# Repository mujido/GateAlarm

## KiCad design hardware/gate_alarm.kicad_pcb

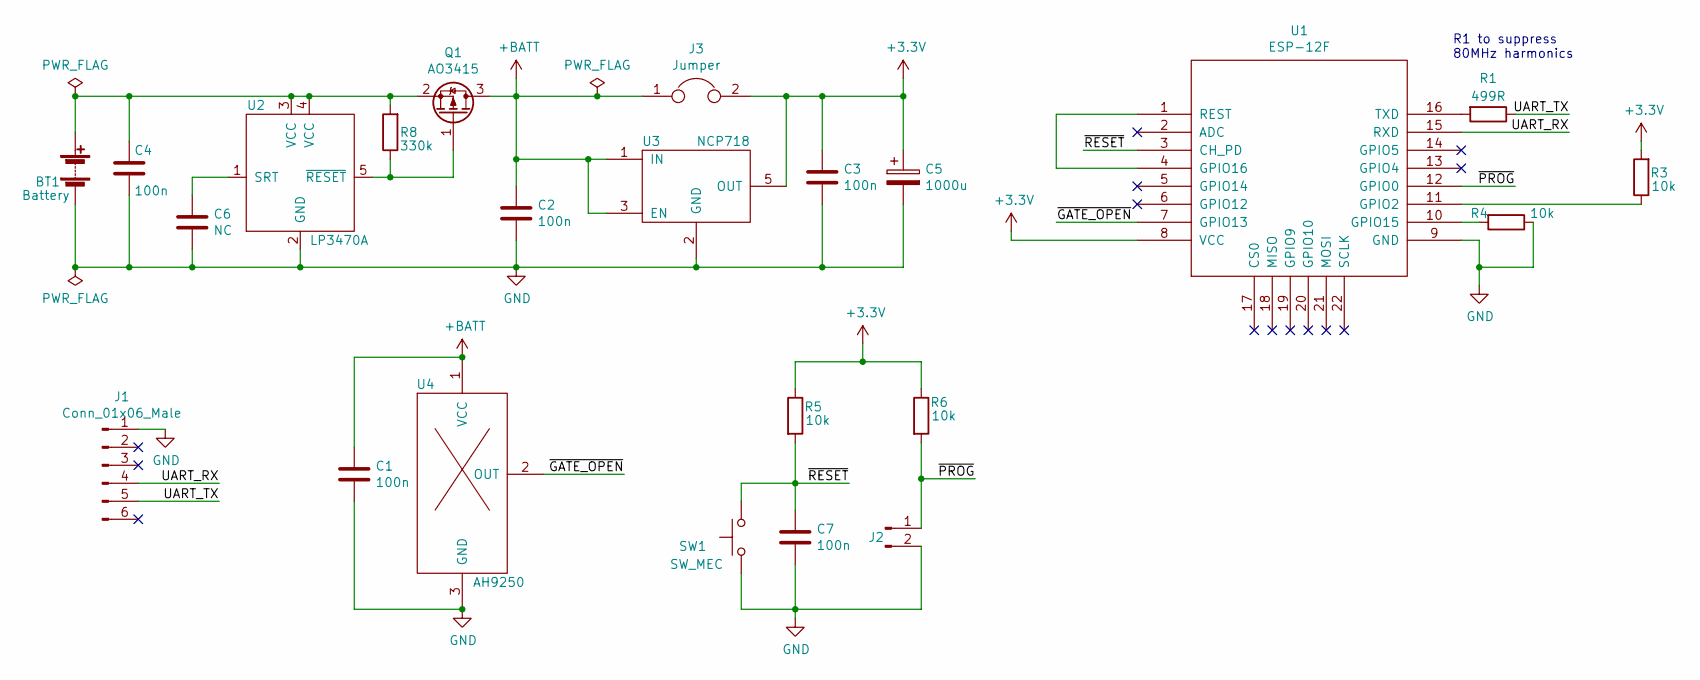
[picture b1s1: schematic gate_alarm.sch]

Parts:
BT1: Battery; JST_XH_B02B-XH-A_02x2.50mm_Straight
C1, C2, C3, C4, C7: 100n; C_0805_HandSoldering
C5: 1000u; CP_Radial_D8.0mm_P3.50mm
C6: NC; C_0805_HandSoldering
J1: Conn_01x06_Male; Pin_Header_Straight_1x06_Pitch2.54mm
J2: Conn_01x02_Male; Pin_Header_Straight_1x02_Pitch2.54mm
J3: Jumper; SolderJumper-2_P1.3mm_Open_Pad1.0x1.5mm
Q1: AO3415; SOT-23_Handsoldering
R1: 499R; R_0805_HandSoldering
R3, R4, R5, R6: 10k; R_0805_HandSoldering
R8: 330k; R_0805_HandSoldering
SW1: SW_MEC; PTS636_THT
U1: ESP-12F; ESP-12E_SMD
U2: LP3470A; SOT-23-5_HandSoldering
U3: NCP718; TSOT-23-5_HandSoldering
U4: AH9250; TO-92S

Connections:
+3V3: C3.1, C5.1, J3.2, R3.2, R5.1, R6.1, U1.8 (VCC), U3.5 (OUT)
+BATT: C1.1, C2.1, J3.1, Q1.3 (D), U3.1 (IN), U3.3 (EN), U4.1 (VCC)
/UART_RX: J1.4, U1.15 (RXD)
/UART_TX: J1.5, R1.1
/~GATE_OPEN: U1.7 (GPIO13), U4.2 (OUT)
/~PROG: J2.1, R6.2, U1.12 (GPIO0)
/~RESET: C7.1, R5.2, SW1.2 (B), U1.3 (CH_PD)
GND: BT1.2 (-), C1.2, C2.2, C3.2, C4.2, C5.2, C6.2, C7.2, J1.1, J2.2, R4.1, SW1.1 (A), U1.9 (GND), U2.2 (GND), U3.2 (GND), U4.3 (GND)
unnamed: BT1.1 (+), C4.1, Q1.2 (S), R8.2, U2.3 (VCC), U2.4 (VCC)
unnamed: C6.1, U2.1 (SRT)
unnamed: Q1.1 (G), R8.1, U2.5 (~RESET)
unnamed: R1.2, U1.16 (TXD)
unnamed: R3.1, U1.11 (GPIO2)
unnamed: R4.2, U1.10 (GPIO15)
unnamed: U1.1 (REST), U1.4 (GPIO16)

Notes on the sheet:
R1 to suppress 80MHz harmonics

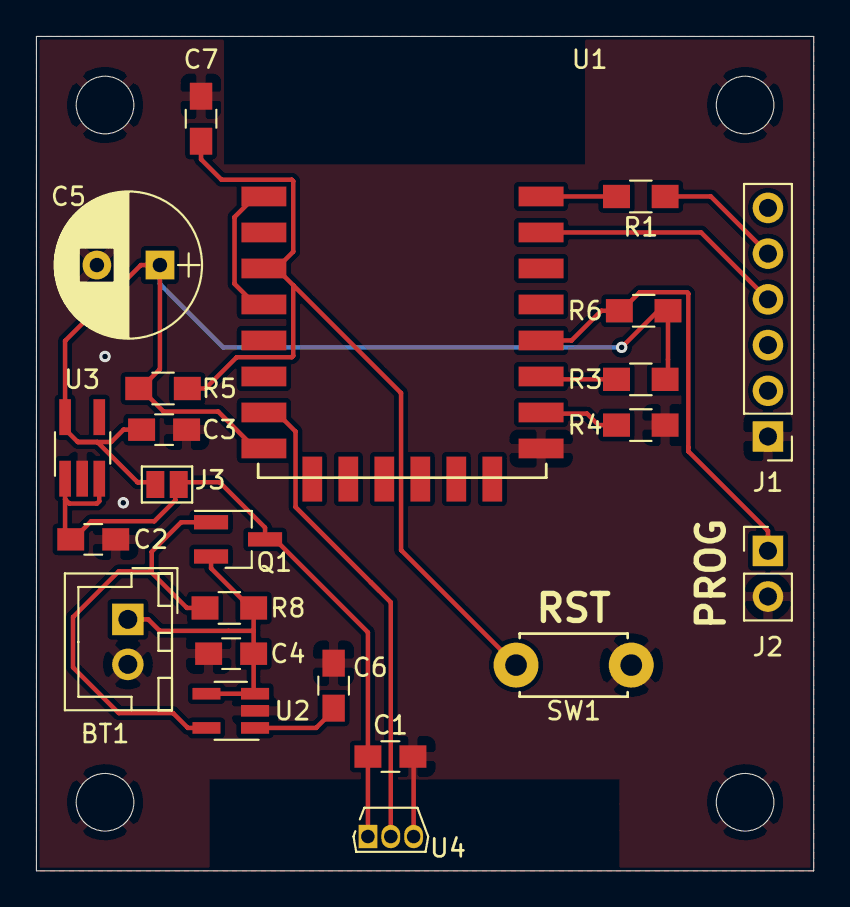
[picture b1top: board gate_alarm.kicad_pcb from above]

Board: 2 copper layers, 43.2 x 46.4 mm, 23 parts (0 on the bottom side), 15 nets.

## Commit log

2019-10-23 Initial commit of code and hardware
2019-10-29 Add datasheets used by hardware
2019-10-29 Remove .vs from repo
2019-10-29 Replacing event system with explicit interrupt handling
2019-10-29 Fix bug in pin toggling code when using -fno-inline
2019-11-17 Initial ESP8266 code commit
2019-11-17 Created Makefile to allow building outside of SDK
2019-11-18 Remove TCP code
2019-12-01 Update hardware for first PCB manufacture
